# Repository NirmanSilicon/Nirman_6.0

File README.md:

# 🏥 Sanjeevani — Intelligent Healthcare & OPD Management Platform

<p align="center">
  <strong>Making Healthcare Smarter, Faster, and More Accessible.</strong>
</p>

<p align="center">
  An AI-powered healthcare navigation, OPD appointment, live queue management, and clinical assistance platform built for <strong>NIRMAN 6.0 — HACKNATION 2026</strong> by <strong>Team crozbit</strong>.
</p>

---

## 📑 Table of Contents

1. [Hackathon Information](#-hackathon-information)
2. [Problem Statement](#-problem-statement)
3. [Our Solution](#-our-solution)
4. [Key Features](#-key-features)
5. [How the System Works](#-how-the-system-works)
6. [System Architecture](#-system-architecture)
7. [Technology Stack](#-technology-stack)
8. [Project Folder Structure](#-project-folder-structure)
9. [Installation and Setup Instructions](#-installation-and-setup-instructions)
10. [Environment Variables](#-environment-variables)
11. [How to Run the Project](#-how-to-run-the-project)
12. [Demo Mode & Simulated Data](#-demo-mode--simulated-data)
13. [API Overview](#-api-overview)
14. [AI / ML Implementation](#-ai--ml-implementation)
15. [Database Design](#-database-design)
16. [Current Implementation Status](#-current-implementation-status)
17. [Limitations and Future Scope](#-limitations-and-future-scope)
18. [Troubleshooting](#-troubleshooting)
19. [Team Members and Contributions](#-team-members-and-contributions)
20. [Hackathon Submission Information](#-hackathon-submission-information)
21. [License](#-license)

---

## 🏆 Hackathon Information

| Field | Details |
| :--- | :--- |
| **Event** | NIRMAN 6.0 — HACKNATION 2026 |
| **Evaluation Stage** | First Progress Evaluation |
| **Team Name** | `crozbit` |
| **Project Name** | Sanjeevani (backend API internally initialized as HealX) |
| **Repository** | `https://github.com/ayusshs/Nirman_6.0` (branch: `crozbit`) |

---

## 🎯 Problem Statement

Patients and hospitals in traditional outpatient (OPD) ecosystems face persistent operational bottlenecks:

- **Long and unpredictable OPD waiting times** with no real-time visibility into queue progression.
- **Inefficient manual appointment and walk-in queue handling**, leading to overcrowding at hospital counters.
- **Difficulty identifying the right hospital or medical specialist** based on symptoms, distance, and current crowd levels.
- **Fragmented medical records and lab reports** that are hard for patients to interpret before consultations.
- **Limited real-time analytics** for hospital administrators to monitor department load and patient feedback.

---

## 💡 Our Solution

**Sanjeevani** unifies hospital discovery, OPD appointment booking, live Socket.IO queue tracking, AI-assisted symptom/report guidance, and hospital admin analytics into a single web platform:

- **Patients** can discover hospitals on an interactive map, get AI-ranked hospital recommendations, book OPD slots, track their live queue position and estimated wait time, upload lab reports/prescriptions for OCR + AI summarization, and chat with an AI healthcare assistant.
- **Hospital Admins & Superadmins** can manage appointments, advance live department queues, view AI-generated operational insights and patient clinical summaries, analyze patient feedback sentiment, and export appointment data as CSV.

> [!NOTE]
> AI-generated guidance and report summaries are informational only and do not replace professional medical diagnosis.

---

## ✨ Key Features

### Implemented in Repository
- **Hospital Discovery & Geospatial Routing**: Browse and search hospitals (`/hospitals`, `/hospitals/$id`), view specialties and doctor slots, and compute driving routes/ETAs using OSRM (`MapService`) and Leaflet maps.
- **Smart OPD Appointment Booking (`/book`)**: Multi-step booking flow with hospital, department/specialty, doctor, and slot selection, backed by `POST /api/patient/book` and walk-in support (`POST /api/walkin_book`).
- **Live OPD Queue Management**: Atomic queue numbering (`QueueService`), live wait-time calculation (`GET /api/patient/active-appointment`, `GET /api/hospital/<hospital_id>/queue`), and real-time `queue_update` broadcasts via Flask-SocketIO.
- **JWT Authentication & Role Separation (`/login`)**: Patient signup/login (`POST /api/auth/signup`, `POST /api/auth/login`) and Admin/Superadmin authentication using `flask-bcrypt` and `PyJWT`.
- **AI Multi-Agent Assistant (`MediBotChat`)**: Intent-routing AI assistant (`POST /api/chat`, `POST /api/ai/chat`) with specialized agents for appointments, queue status, hospital recommendations, report summaries, and medical Q&A, backed by local Ollama (`gemma3:4b`), RAG over `backend/knowledge/`, and rule-based offline fallbacks.
- **Medical Report Upload & AI Summary**: Upload PDFs or images (`POST /api/patient/upload_report`) parsed via `pdfplumber` / `easyocr` and summarized via Ollama.
- **Admin & Superadmin Operations**: Queue advancement (`POST /api/admin/queue/serve`), appointment status management, AI patient clinical briefs, feedback sentiment/topic analytics, CSV export, and platform-wide superadmin management.

### UI-Simulated / In-Progress Modules
- **Digital Pharmacy (`/pharmacy`)**: Interactive medicine catalog, cart drawer, and multi-step checkout UI using client-side data (`medicineData.ts`).
- **SOS Emergency Center (`/emergency`)**: First-aid guides and simulated ambulance dispatch telemetry using mock hospital coordinates.
- **Patient Portal Enhancements (`/dashboard`)**: Digital health card / ABHA-style ID display and vitals UI alongside live backend appointments and reports.

---

## 🔄 How the System Works

```mermaid
flowchart LR
    U[Patient] -->|1. Register / Login| Auth[JWT Auth API]
    U -->|2. Search Hospitals & Symptoms| Rec[Recommendation Engine + OSRM]
    U -->|3. Book OPD Slot| Book[POST /api/patient/book]
    Book --> Q[QueueService: Assign Token & Predict Wait]
    Q -->|Socket.IO queue_update| Dash[Patient Dashboard]
    Admin[Hospital Admin] -->|4. Serve Next Patient| Serve[POST /api/admin/queue/serve]
    Serve -->|Socket.IO queue_update| Dash
    U -->|5. Upload Lab Report / Chat| AI[AI Router + OCR + Ollama + RAG]
```

1. **Authentication**: A patient signs up or logs in at `/login`; the backend issues a 24-hour HS256 JWT stored in `localStorage`.
2. **Hospital Discovery**: The frontend calls `GET /api/hospital/` (auto-seeding sample Bhubaneswar hospitals via `POST /api/hospital/seed` if the database is empty) and `GET /api/hospital/search` for symptom-to-department + ML-ranked recommendations.
3. **Appointment & Queue Assignment**: Booking an appointment atomically increments `total_in_queue` in MongoDB, estimates wait time using `QueuePredictor` (XGBoost or rule-based fallback), and emits a Socket.IO `queue_update` event.
4. **Live Tracking & Admin Serving**: As admins advance the queue via `POST /api/admin/queue/serve` or update appointment statuses, the patient's `people_ahead` and `wait_time_predicted` recalculate live.
5. **AI & Report Assistance**: Patient chat messages pass through `AIRouter` (intent detection + conversation memory + RAG context + Ollama/fallback); uploaded reports pass through `ReportAnalyzer` (`pdfplumber` / `easyocr` + Ollama).

---

## 🏗️ System Architecture

```mermaid
flowchart TD
    subgraph Client ["Frontend (TanStack Start + React + Vite)"]
        UI[Pages: /, /hospitals, /book, /dashboard, /pharmacy, /emergency, /login]
        Map[Leaflet Interactive Map]
        Chat[MediBotChat Widget]
    end

    subgraph Server ["Backend (Flask + Flask-SocketIO)"]
        Routes[Blueprints: auth, patient, hospital, api, admin, superadmin, ai]
        Services[Services: QueueService, MapService, AIService]
        AIRouter[AI Router & Agents + RAG]
        ML[ML Predictors: Disease, Queue, Recommendation, Feedback]
    end

    subgraph Data ["Data & External Services"]
        Mongo[(MongoDB)]
        Redis[(Redis - Optional SocketIO Queue)]
        Ollama[Local Ollama LLM - gemma3:4b]
        OSRM[OSRM Routing API]
    end

    UI --> Routes
    Map --> Routes
    Chat --> Routes
    Routes --> Services
    Routes --> AIRouter
    Services --> ML
    Routes --> Mongo
    Services --> Mongo
    Services --> OSRM
    Server --> Redis
    AIRouter --> Ollama
```

- **Frontend (`frontend/`)**: Built with **TanStack Start**, **TanStack Router**, **TanStack Query**, **React 19**, **TypeScript**, and **Tailwind CSS v4**. Communicates with the Flask backend at `http://localhost:5000/api` (`frontend/src/lib/api.ts`).
- **Backend (`backend/`)**: Modular **Flask** application factory (`create_app()` in `backend/app/__init__.py`) registering 7 blueprints (`/api/auth`, `/api/patient`, `/api/hospital`, `/api`, `/api/admin`, `/api/superadmin`, `/api/ai`) with **Flask-SocketIO** for real-time queue events.
- **Database**: **MongoDB** via `pymongo` (`patients`, `hospitals`, `appointments`, `queue`, `queue_history`, `reports`, `admins`, `feedback` collections). **Redis** is optional for Socket.IO message queuing and falls back to an in-memory queue if unavailable.
- **AI/ML Layer**: Combines 4 `.joblib` scikit-learn/XGBoost/LightGBM models in `trained_models/`, a JSON-backed RAG store (`backend/trained_models/rag_index.json`), `pdfplumber`/`easyocr` document extraction, and local **Ollama** inference with deterministic fallbacks.

---

## 🛠️ Technology Stack

| Layer | Technologies Verified in Repository |
| :--- | :--- |
| **Frontend Framework** | React 19, TypeScript, TanStack Start, TanStack Router, TanStack Query, Vite 8 |
| **UI & Visualization** | Tailwind CSS v4, Radix UI, Lucide React, Recharts, Leaflet |
| **Forms & Validation** | React Hook Form, Zod |
| **Backend Framework** | Python, Flask, Flask-SocketIO, Flask-CORS, Flask-Bcrypt, PyJWT, Gunicorn |
| **Database & Messaging** | MongoDB (`pymongo`), Redis (optional Socket.IO message queue) |
| **AI / LLM & RAG** | Ollama (`gemma3:4b` default), `sentence-transformers`, `anthropic` (listed in `requirements.txt`), custom JSON RAG store |
| **ML & Data** | `scikit-learn`, `xgboost`, `lightgbm`, `pandas`, `numpy`, `joblib` |
| **OCR & PDF Parsing** | `easyocr`, `pdfplumber` |
| **Geospatial Routing** | OSRM (`router.project-osrm.org`), Leaflet |

---

## 📂 Project Folder Structure

```text
Nirman_6.0/
├── crozbit.txt                        # Hackathon & team identifier
├── trained_models/                    # Pre-trained ML model artifacts (.joblib)
│   ├── disease_risk_model.joblib
│   ├── feedback_sentiment_model.joblib
│   ├── queue_model.joblib
│   └── recommendation_model.joblib
│
├── backend/
│   ├── Procfile                       # Gunicorn process definition
│   ├── requirements.txt               # Python dependencies
│   ├── run.py                         # Flask-SocketIO entry point (port 5000)
│   ├── seed_superadmin.py             # Script to seed default superadmin
│   ├── test_*.py                      # Backend API, AI, routing, and signup test scripts
│   ├── knowledge/                     # RAG knowledge base (.txt files: faqs, hospitals, policies)
│   ├── ml/                            # Training scripts for the 4 ML models
│   ├── ml_models/train.py             # Additional ML training script
│   ├── trained_models/rag_index.json  # Pre-indexed RAG knowledge file
│   └── app/
│       ├── __init__.py                # Flask app factory, MongoDB, SocketIO, blueprints
│       ├── config.py                  # Environment configuration loader
│       ├── ai/                        # AI router, agents, Ollama client, RAG, ML predictors
│       ├── models/                    # MongoDB data access classes
│       ├── routes/                    # Flask blueprints (auth, patient, hospital, api, admin, superadmin, ai)
│       ├── services/                  # QueueService, MapService, AIService
│       └── utils/                     # Synthetic dataset generator
│
└── frontend/
    ├── package.json                   # Node dependencies & Vite scripts
    ├── vite.config.ts
    ├── tsconfig.json
    ├── public/                        # Static assets (logo.png, hero-video.mp4)
    └── src/
        ├── router.tsx                 # TanStack Router setup
        ├── routeTree.gen.ts           # Generated route tree
        ├── components/                # UI components (HospitalMap, MediBotChat, CameraCapture, etc.)
        ├── hooks/                     # Custom React hooks
        ├── lib/                       # API client (api.ts), mockData.ts, medicineData.ts, utils
        └── routes/                    # File-based routes (/, /login, /dashboard, /book, /hospitals, /pharmacy, /emergency, /about)
```

---

## ⚙️ Installation and Setup Instructions

### Prerequisites
- **Python 3.10+**
- **Node.js 18+** and **npm**
- **MongoDB** (local MongoDB Community Server or a MongoDB connection URI)
- **Ollama** (optional, for local LLM chat & report summarization; backend falls back to rule-based responses if Ollama is not running)
- **Redis** (optional; backend falls back to simple in-memory Socket.IO queue if unavailable)

### 1. Clone the Repository
```powershell
git clone https://github.com/ayusshs/Nirman_6.0.git
cd Nirman_6.0
```

### 2. Backend Setup (Windows PowerShell)
```powershell
cd backend
python -m venv .venv
.\.venv\Scripts\Activate.ps1
pip install -r requirements.txt
```

Create a `.env` file inside `backend/` (see [Environment Variables](#-environment-variables)).

*(Optional)* Seed the default superadmin account:
```powershell
python seed_superadmin.py
```

### 3. Frontend Setup (Windows PowerShell)
Open a new terminal in the repository root:
```powershell
cd frontend
npm install
```

---

## 🔐 Environment Variables

Create `backend/.env` using placeholders — **never commit `.env` or real credentials**:

```env
# Flask & JWT Security
SECRET_KEY=your_random_secret_key_here

# Database (Required for backend persistence)
MONGO_URI=mongodb://localhost:27017/sanjeevani

# Optional Redis for SocketIO message queue
REDIS_URL=redis://localhost:6379/0

# Optional Local LLM (Ollama)
LLM_PROVIDER=ollama
OLLAMA_BASE_URL=http://localhost:11434
OLLAMA_MODEL=gemma3:4b
DEFAULT_MODEL=gemma3:4b

# Optional External Keys (referenced in Config)
ANTHROPIC_API_KEY=your_anthropic_api_key_if_used
TWILIO_SID=your_twilio_sid_if_used
TWILIO_AUTH=your_twilio_auth_token_if_used
TWILIO_PHONE=your_twilio_phone_if_used
```

> [!IMPORTANT]
> `frontend/src/lib/api.ts` currently sets `API_BASE_URL = "http://localhost:5000/api"`. Ensure the backend runs on port `5000` during local development.

---

## ▶️ How to Run the Project

### Start the Backend Server
```powershell
cd backend
.\.venv\Scripts\Activate.ps1
python run.py
```
The Flask-SocketIO server starts on `http://localhost:5000`. Visiting `http://localhost:5000/` returns `{"message": "Welcome to HealX API"}`.

### Start the Frontend Development Server
```powershell
cd frontend
npm run dev
```
The Vite / TanStack Start dev server starts on `http://localhost:5173` (or the port printed in your terminal).

### Optional: Start Ollama for Local LLM Features
```powershell
ollama pull gemma3:4b
ollama serve
```

---

## 🧪 Demo Mode & Simulated Data

- **Auth-Gated Frontend Routes**: In `frontend/src/routes/__root.tsx`, navigating to `/dashboard` or `/book` checks `isLoggedIn()` (`localStorage.getItem("token")`) and redirects unauthenticated users to `/login`.
- **Automatic Hospital Seeding**: When `fetchHospitals()` receives an empty list from `GET /api/hospital/`, it automatically calls `POST /api/hospital/seed` to populate 3 sample Bhubaneswar hospitals (`SUM Hospital`, `AIIMS Bhubaneswar`, `Capital Hospital`).
- **Mock UI Enrichment (`frontend/src/lib/mockData.ts`)**: Backend hospital records are merged with mock bed counts, review counts, distances, and placeholder images for UI display.
- **Simulated Modules**:
  - `/pharmacy` uses static medicine catalog data (`medicineData.ts`) and a simulated checkout flow (e.g., coupon `SANJEEVANI30`, 3D card UI).
  - `/emergency` displays simulated ambulance tracking telemetry and static first-aid instructions.
  - `ReportAnalyzer` falls back to sample lab/MRI text if `EasyOCR` fails to initialize on an image upload.

---

## 📡 API Overview

All routes are mounted under `/api` (see `backend/app/__init__.py` and `backend/app/routes/`):

| Prefix | Method & Endpoint | Description |
| :--- | :--- | :--- |
| `/` | `GET /` | Health/welcome check |
| **Auth** (`/api/auth`) | `POST /api/auth/signup` | Register a new patient account |
| | `POST /api/auth/login` | Authenticate patient or admin/superadmin, returns JWT |
| **Patient** (`/api/patient`) | `GET /api/patient/profile` | Fetch patient profile, appointments, reports (JWT required) |
| | `PUT /api/patient/profile` | Update patient profile fields (JWT required) |
| | `GET /api/patient/active-appointment` | Fetch active appointment with live queue wait recalculation |
| | `GET /api/patient/appointments` | List all patient appointments |
| | `GET /api/patient/appointment/<booking_id>` | Get single appointment + embedded hospital info |
| | `POST /api/patient/book` | Book OPD appointment & assign queue token |
| | `POST /api/patient/upload_report` | Upload PDF/image report for OCR + AI summary |
| | `GET /api/patient/reports` | List uploaded patient reports |
| **Hospital** (`/api/hospital`) | `POST /api/hospital/seed` | Seed sample hospitals into MongoDB |
| | `GET /api/hospital/` | List all hospitals |
| | `GET /api/hospital/search` | Search & AI-rank hospitals by disease, state, query, `lat`/`lng` |
| | `GET /api/hospital/<hospital_id>` | Get hospital details and doctors |
| | `PUT /api/hospital/<hospital_id>` | Update hospital details |
| | `GET /api/hospital/<hospital_id>/route` | Get OSRM driving route from `start_lat`, `start_lng` |
| | `GET /api/hospital/<hospital_id>/queue` | Get live queue metrics per department |
| **Public / AI** (`/api`, `/api/ai`) | `POST /api/walkin_book` | Book a walk-in appointment without patient login |
| | `POST /api/chat` | Send message to `AIRouter` (with rule-based fallback) |
| | `POST /api/ai/chat` | Direct `AIRouter` chat endpoint |
| | `GET /api/reverse-geocode` | Reverse geocode `lat`, `lng` via `MapService` |
| **Admin** (`/api/admin`) | `GET /api/admin/appointments` | List appointments (filterable by `status`, `hospital_id`) |
| | `PUT /api/admin/appointments/<booking_id>/status` | Update appointment status & log queue history |
| | `POST /api/admin/queue/serve` | Increment `current_serving` & broadcast Socket.IO update |
| | `GET /api/admin/analytics` | Hospital appointment counts, queues, & AI insights |
| | `GET /api/admin/patient/<patient_id>/ai_summary` | Generate doctor brief via DiseasePredictor + Ollama |
| | `GET /api/admin/feedback_analytics` | Analyze review sentiment & common topics |
| | `GET /api/admin/export` | Export appointments as CSV |
| **Superadmin** (`/api/superadmin`) | `GET /api/superadmin/dashboard`, `/analytics` | Platform-wide counts (Superadmin JWT required) |
| | `GET / POST /api/superadmin/hospitals`, `PUT .../<id>` | Manage hospitals |
| | `GET / POST /api/superadmin/admins` | Manage hospital admins |

---

## 🤖 AI / ML Implementation

1. **Trained ML Models (`trained_models/*.joblib`, trained via `backend/ml/train_*.py` on synthetic/generated data)**:
   - **Disease Risk Predictor (`disease_risk_model.joblib`)**: `RandomForestClassifier` predicting `Low Risk`, `Medium Risk`, or `High Risk` from `age`, `bmi`, `sys_bp`, `sugar`, `smoking`, `exercise`, and `family_history` (falls back to a weighted rule score if the bundle is absent).
   - **Queue Wait-Time Predictor (`queue_model.joblib`)**: `XGBRegressor` predicting wait time in minutes using `people_ahead`, encoded `department`, `hour`, `weekday`, `holiday`, `emergency`, and `doctor_average_time` (falls back to `people_ahead * doctor_avg_time`).
   - **Hospital Recommendation Engine (`recommendation_model.joblib`)**: `LGBMRegressor` ranking hospitals using `distance`, `rating`, `queue_length`, `crowd_level`, `doctor_experience`, and `availability`.
   - **Feedback Sentiment Analyzer (`feedback_sentiment_model.joblib`)**: `TfidfVectorizer` + `MultinomialNB` pipeline classifying reviews as `positive`, `neutral`, or `negative`, paired with keyword-based topic extraction (`Waiting Time`, `Doctor Care`, `Billing`, `Cleanliness`, `General`).
2. **Multi-Agent AI Router & RAG (`backend/app/ai/`)**:
   - `AIRouter` classifies user messages into `appointment`, `queue_status`, `hospital_recommendation`, `report_summary`, `wallet_query`, or `medical_question` and dispatches to specialized agents.
   - `ContextBuilder` injects patient database context and RAG snippets from `backend/trained_models/rag_index.json` (built from `backend/knowledge/`).
   - `OllamaClient` queries `http://localhost:11434/api/chat` (`gemma3:4b` default) and gracefully degrades to keyword-based responses when Ollama is offline.
3. **Report Analyzer (`backend/app/ai/report_analyzer.py`)**:
   - Extracts text from PDFs (`pdfplumber`) and images (`easyocr`) and sends up to 1,200 characters to Ollama for a patient-friendly summary.

---

## 🗄️ Database Design

The backend uses **MongoDB** (`pymongo`) with the following collections:

| Collection | Key Fields & Purpose |
| :--- | :--- |
| `patients` | `patient_id` (`PAT-...`), `name`, `email`, `password_hash`, `gender`, `dob`, `bloodGroup`, `phone`, `emergency_contact`, `address`, `aadhar`, `insurance`, `tss_points`, `medicines`, `reports`, `bills` |
| `hospitals` | `hospital_id` (`HOSP-...`), `name`, `logo`, `address`, `location` (`city`, `state`, `lat`, `lng`), `workingHours`, `phone`, `email`, `specialties`, `departments`, `crowd_level`, `rating`, `doctors` |
| `appointments` | `booking_id` (`HLX-YYYYMMDD-DEPT-...`), `patient_id`, `hospital_id`, `doctor_id`, `department`, `slot_time`, `queue_number`, `status`, `wait_time_predicted`, `type`, `symptoms`, `paymentMode`, `paymentStatus`, `booked_at` |
| `queue` | `hospital_id`, `department`, `current_serving`, `total_in_queue`, `avg_time_per_patient`, `last_updated` (updated atomically via `find_one_and_update`) |
| `queue_history` | Event log of queue actions (`joined`, `served`, `completed`, `cancelled`, `no-show`) |
| `reports` | `patient_id`, `filename`, `extracted_text`, `ai_summary`, `uploaded_at` |
| `admins` | `admin_id` (`ADM-...`), `name`, `email`, `password_hash`, `role` (`admin` / `superadmin`), `hospitalId` |
| `feedback` | Patient review texts and departments used by `/api/admin/feedback_analytics` |

---

## 📊 Current Implementation Status

| Module | Status | Notes |
| :--- | :--- | :--- |
| Patient Auth (Signup / Login / JWT) | ✅ Implemented | `auth.py`, `login.tsx` |
| Hospital Listing, Seeding & Search | ✅ Implemented | `hospital.py`, `HospitalMap.tsx`, `mockData.ts` UI merge |
| OPD Booking & Live Queue Tracking | ✅ Implemented | `patient.py`, `QueueService`, Socket.IO |
| Admin Queue Serving, Analytics & CSV Export | ✅ Implemented | `admin.py`, `superadmin.py` |
| AI Router, ML Models & Report Analyzer | ✅ Implemented | Uses local Ollama + `.joblib` models trained on synthetic data; includes fallbacks |
| Digital Pharmacy (`/pharmacy`) | 🟡 Simulated UI | Static catalog (`medicineData.ts`) & simulated checkout |
| SOS Emergency & Ambulance Tracking (`/emergency`) | 🟡 Simulated UI | Static first-aid & mock ambulance telemetry |
| Android / Amazfit Bip 5 Wearable Integration | 🔵 Planned | Not yet present in repository |

---

## 🔭 Limitations and Future Scope

### Current Limitations
- ML models (`disease_risk_model`, `recommendation_model`, `feedback_sentiment_model`, `queue_model`) are trained on synthetic/generated datasets rather than live hospital clinical datasets.
- Frontend `API_BASE_URL` is hardcoded to `http://localhost:5000/api` in `frontend/src/lib/api.ts`.
- Admin and Superadmin routes have dedicated backend APIs, while the frontend primarily focuses on the patient portal.
- Pharmacy and Emergency modules currently operate on simulated frontend data.

### Future Scope
- Persist pharmacy orders and live ambulance dispatch telemetry in MongoDB.
- Build dedicated frontend portals for Hospital Admins and Superadmins.
- Add Android companion app integration for wearable queue/vibration alerts (e.g., Amazfit Bip 5).
- Retrain ML models on anonymized real-world OPD datasets and add automated CI tests.

---

## 🛠️ Troubleshooting

- **MongoDB Connection Error (`Error connecting to MongoDB`)**:
  - Verify MongoDB is running locally or your `MONGO_URI` in `backend/.env` is valid and reachable.
- **Redis Warning (`Could not connect to Redis, falling back to simple queue`)**:
  - Non-fatal. Flask-SocketIO automatically falls back to an in-memory queue for single-instance local development.
- **Ollama Offline Fallback**:
  - If Ollama is not running on `http://localhost:11434`, `OllamaClient` automatically returns rule-based fallback responses so `/api/chat` and `/api/patient/upload_report` do not crash.
- **Redirected to `/login` when opening `/dashboard` or `/book`**:
  - Expected behavior (`__root.tsx`). Sign up a new patient account at `/login` first to obtain a JWT token.
- **Empty Hospital List**:
  - Ensure the Flask backend is running on port `5000`; `fetchHospitals()` will automatically trigger `POST /api/hospital/seed` on first load.

---

## 👥 Team Members and Contributions

**Team:** `crozbit` (NIRMAN 6.0 — HACKNATION 2026)

| Member Name | Role / Focus Area | Contributions |
| :--- | :--- | :--- |
| `[Member 1 Name]` | Frontend & UI/UX | TanStack Start / React frontend, Leaflet maps, OPD booking & portal UI |
| `[Member 2 Name]` | Backend & Database | Flask APIs, MongoDB models, JWT auth, Socket.IO queue service |
| `[Member 3 Name]` | AI / ML & RAG | Multi-agent AI router, Ollama integration, `.joblib` ML models, OCR report analyzer |
| `[Member 4 Name]` | Testing & Integration | End-to-end testing, deployment config, documentation |

*(Replace placeholders above with actual team member names and verified role splits before final submission.)*

---

## 📝 Hackathon Submission Information

- **Hackathon**: NIRMAN 6.0 — HACKNATION 2026
- **Submission Milestone**: First Progress Evaluation
- **Team**: `crozbit`
- **Active Branch**: `crozbit`

---

## 📄 License

No `LICENSE` file is currently present in this repository. Add an appropriate open-source license (e.g., MIT) if required for final submission.

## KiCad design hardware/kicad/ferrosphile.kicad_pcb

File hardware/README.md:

# Ferrosphile hardware: carrier PCB

A 2-layer carrier board, 100 × 72 mm, all through-hole. The ESP32 DevKit, the tilt board and the compasses plug in, so nothing on the board is hard to solder.

- Schematic: [docs/ferrosphile-schematic.pdf](docs/ferrosphile-schematic.pdf)
- PCB layout (both copper layers): [docs/ferrosphile-pcb-layout.pdf](docs/ferrosphile-pcb-layout.pdf)
- Gerbers for ordering: [fabrication/ferrosphile-gerbers.zip](fabrication/ferrosphile-gerbers.zip)
- BOM: [fabrication/ferrosphile-bom.csv](fabrication/ferrosphile-bom.csv)

Checked in KiCad 8: **ERC 0 errors, DRC 0 violations, 0 unrouted pads, PCB matches schematic.**

## Folder layout

```
hardware/
  kicad/          KiCad 8 project (open ferrosphile.kicad_pro)
    ferrosphile.kicad_sym   custom symbols: ESP32 DevKit V1, GY-521
    ferrosphile.pretty/     custom footprint: ESP32 DevKit V1 (2 x 1x15 headers)
  fabrication/    Gerbers + drill files (zip), BOM
  docs/           schematic PDF/SVG/PNG, PCB previews
```

## What is on the board

| Block | Parts | What it does |
|---|---|---|
| LC oscillator | U1 74HC04, R1 1M, R2 1k, C1/C2 100n film, J1 coil | Pierce oscillator around the search coil, about 42 kHz. Metal near the coil shifts the frequency. |
| Buffer | U1B | Squares the signal for the ESP32 pulse counter |
| Brain | U2 ESP32 DevKit V1 (30-pin) | Reads all sensors, talks to a laptop over USB |
| Gradiometer | J2 tip compass, J3 top compass (GY-271) | Two QMC5883L boards. Bottom minus top cancels Earth's field. |
| Tilt | M1 GY-521 (MPU6050) | Corrects for how the probe is held |
| Display | J4 (optional) | 0.96" SSD1306 OLED |
| Controls | SW1 ZERO, SW2 RECORD | Zero (learn "nothing here") and record buttons |
| Power | J5, SW3, D1 1N5819 | Optional 5 V battery input. USB alone also works. |

## Pin map

| Net | ESP32 pin | Connects to |
|---|---|---|
| OSC_FREQ | GPIO34 | U1 pin 4 (buffered oscillator) |
| SDA0 / SCL0 | GPIO21 / GPIO22 | J2 tip compass (0x0D), M1 MPU6050 (0x68), J4 OLED (0x3C) |
| SDA1 / SCL1 | GPIO25 / GPIO26 | J3 top compass (0x0D) |
| BTN_ZERO | GPIO14 | SW1 to GND (internal pull-up) |
| BTN_REC | GPIO13 | SW2 to GND (internal pull-up) |
| VIN | VIN | J5 battery, through SW3 and D1 |
| +3V3 | 3V3 | U1 and all sensors |

Both compasses use address 0x0D, so each one gets its own I2C bus.

Connector pin order, printed on the board:
- J2 and J3: 3V3, GND, SCL, SDA
- J4: GND, VCC, SCL, SDA (the usual OLED order)
- J5: + then −

## Order the PCB

1. Upload `fabrication/ferrosphile-gerbers.zip` to JLCPCB, PCBWay or any PCB maker.
2. Settings: 2 layers, 1.6 mm, 100 × 72 mm, 1 oz copper, HASL. Any colour.
3. Smallest track is 0.3 mm and the smallest gap is 0.25 mm, so the cheapest standard option works.

**Before you order, measure your ESP32 board.** The footprint expects the two header rows 25.4 mm apart (DOIT DevKit V1, 30-pin). Some clones are 22.86 mm. If yours differs, edit `ferrosphile.pretty/ESP32_DevKit_V1_30pin.kicad_mod`.

## Extra parts to solder (not in the BOM)

- 2 × 1x15 female headers, 2.54 mm, for the ESP32
- 1 × 1x8 female header for the GY-521 (M1 is a socket)
- 1 × DIP-14 IC socket for the 74HC04
- 4-wire cables for the two compasses, twisted 2-wire cable for the coil

## Assembly order

1. Lowest parts first: R1, R2, D1 (stripe to the "K" side), C1, C2, C3.
2. DIP-14 socket, then buttons and the slide switch.
3. Screw terminals J1 and J5, pin headers J2, J3, J4.
4. Female headers for the ESP32 and the GY-521.
5. Before plugging anything in: check with a multimeter that 3V3 and GND are **not** shorted.
6. Plug in the 74HC04 (notch to the top), the ESP32 (USB end to the left) and the GY-521.

## Wiring the probe

- **Coil (J1):** 35–40 turns of 28 SWG enamelled wire on a 10 cm ring, about 250–300 µH. Scrape the enamel at the ends. Use twisted wire to the board.
- **Tip compass (J2):** in the probe tip, next to the coil.
- **Top compass (J3):** about 30 cm higher up the pole. The bigger the gap, the better the Earth's field cancels.
- Keep steel screws and magnets away from both compasses.

## Design notes

- C1 and C2 must be film capacitors. Ceramic ones drift with heat and cause fake readings.
- GPIO34 is input-only. That is fine here, because it only reads the oscillator.
- A ground pour covers both layers, except under the ESP32 antenna (keep-out zone).
- D1 stops USB power flowing back into the battery board when both are connected.
- Power nets use 0.5 mm tracks where there is room.

## Edit in KiCad

Install KiCad 8 or newer, then open `kicad/ferrosphile.kicad_pro`. The project carries its own symbol and footprint library, so it opens without extra setup.

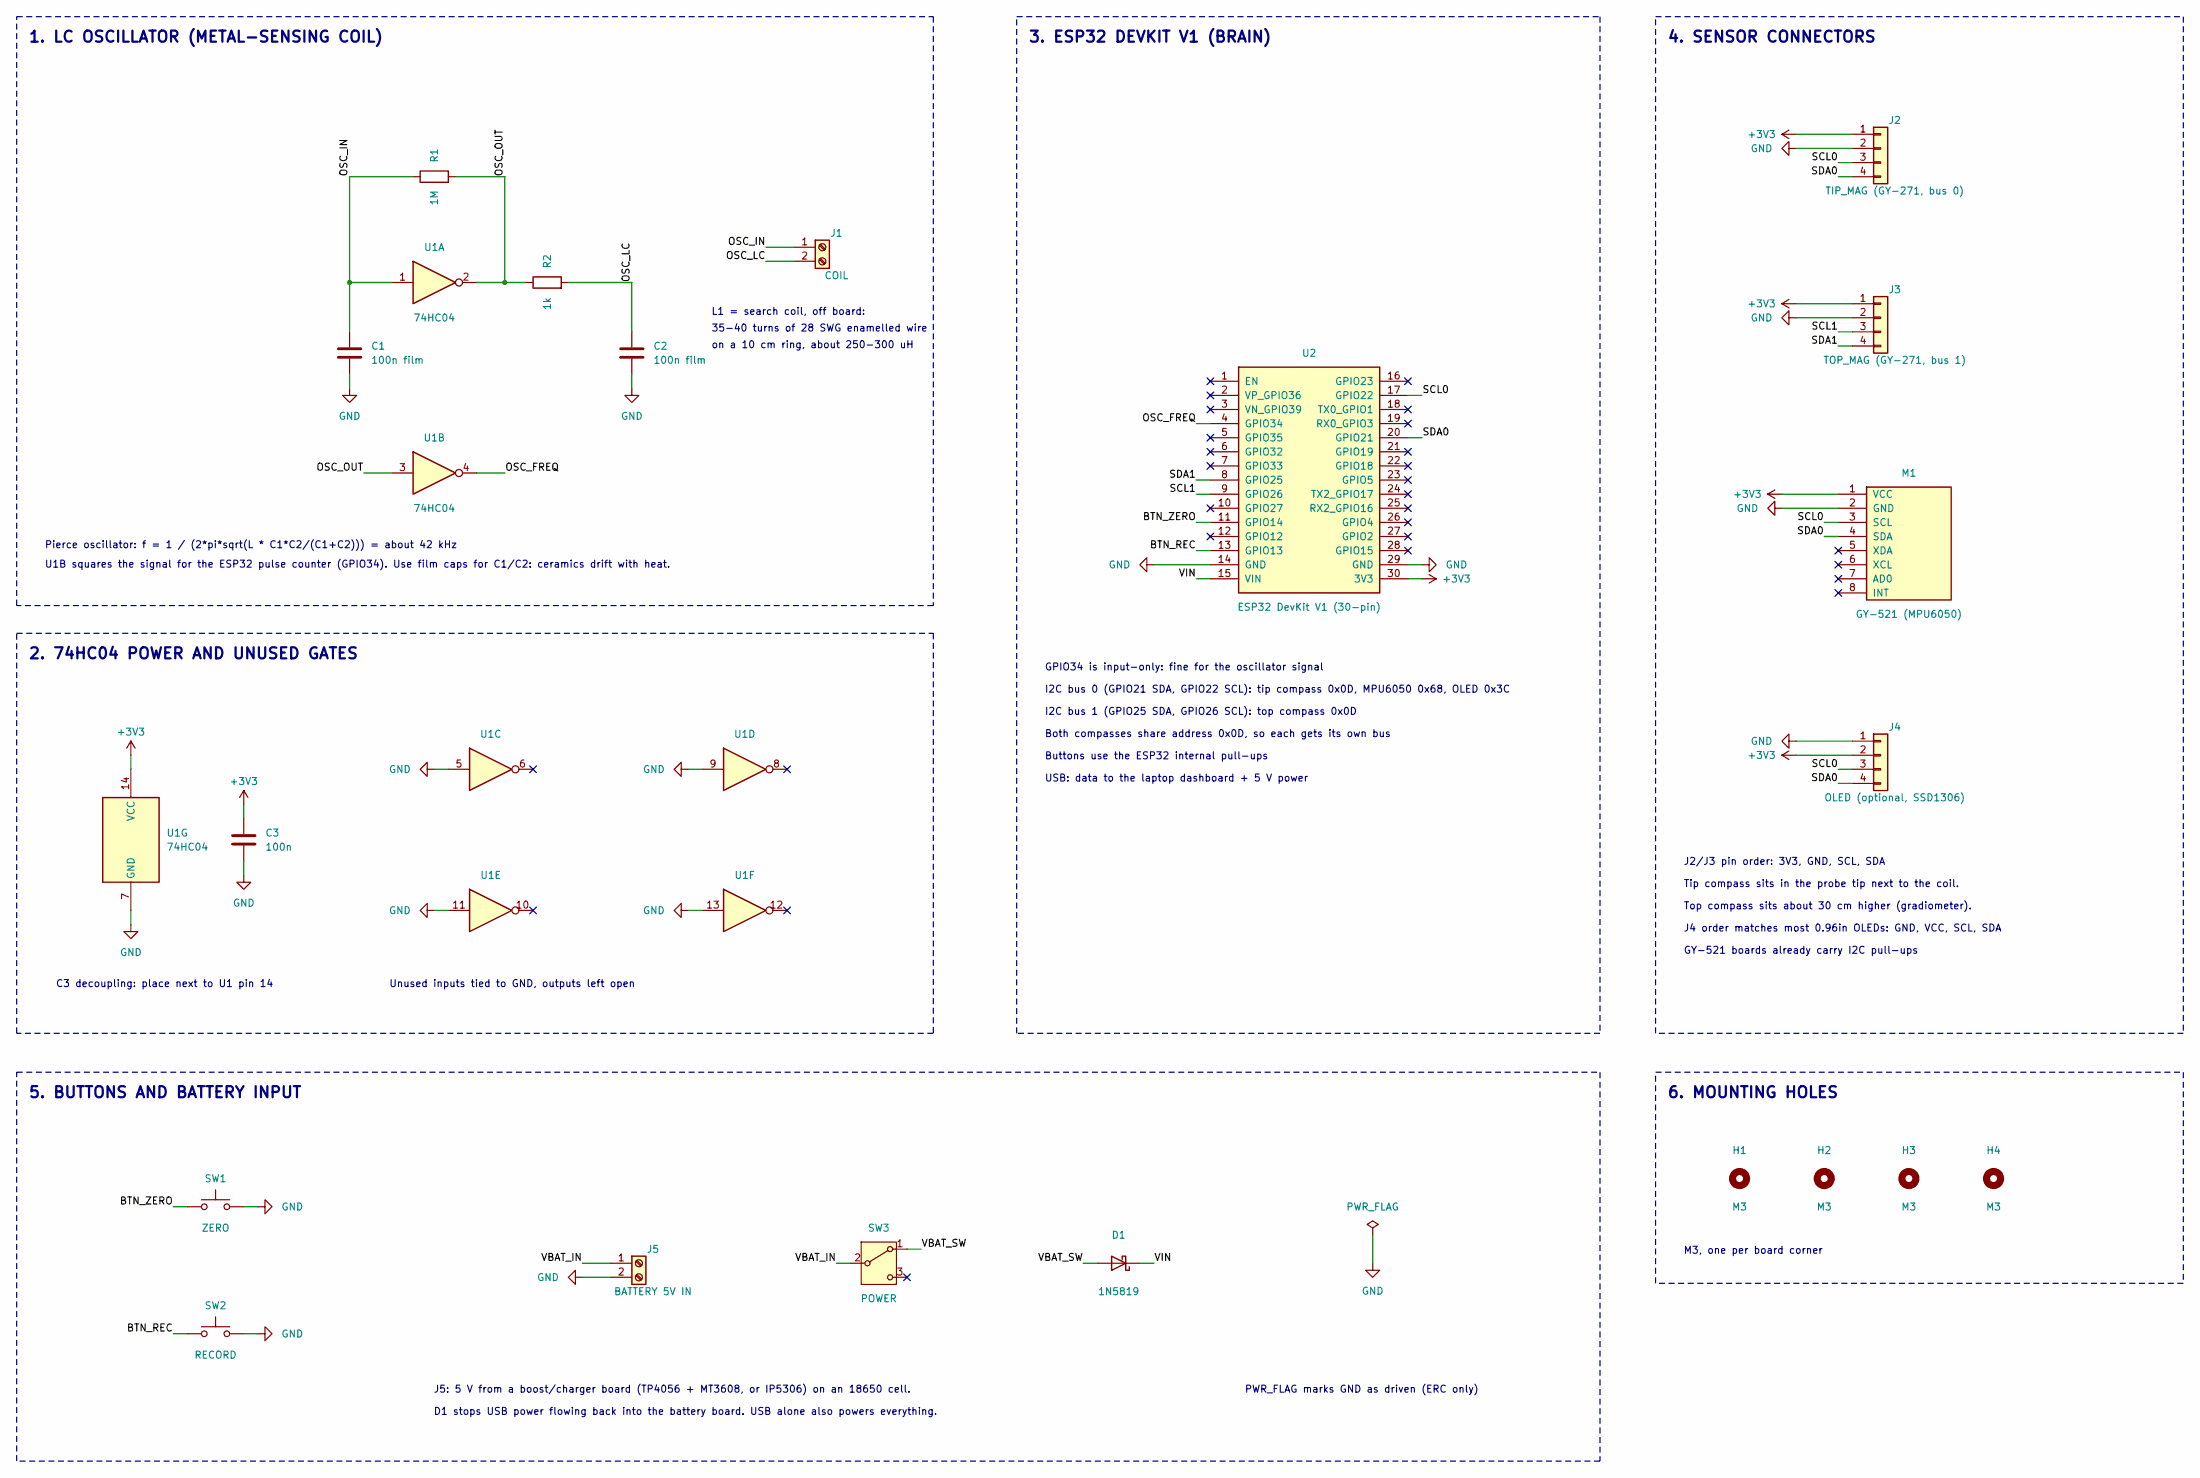
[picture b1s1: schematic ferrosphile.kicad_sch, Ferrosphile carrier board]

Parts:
C1, C2: 100n film; C_Rect_L7.2mm_W3.5mm_P5.00mm_FKS2_FKP2_MKS2_MKP2
C3: 100n; C_Disc_D5.0mm_W2.5mm_P5.00mm
D1: 1N5819; D_DO-41_SOD81_P10.16mm_Horizontal
H1, H2, H3, H4: M3; MountingHole_3.2mm_M3
J1: COIL; TerminalBlock_Phoenix_MKDS-1,5-2-5.08_1x02_P5.08mm_Horizont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
J2: TIP_MAG (GY-271, bus 0); PinHeader_1x04_P2.54mm_Vertical
J3: TOP_MAG (GY-271, bus 1); PinHeader_1x04_P2.54mm_Vertical
J4: OLED (optional, SSD1306); PinHeader_1x04_P2.54mm_Vertical
J5: BATTERY 5V IN; TerminalBlock_Phoenix_MKDS-1,5-2-5.08_1x02_P5.08mm_Horizont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
M1: GY-521 (MPU6050); PinSocket_1x08_P2.54mm_Vertical
R1: 1M; R_Axial_DIN0207_L6.3mm_D2.5mm_P10.16mm_Horizontal
R2: 1k; R_Axial_DIN0207_L6.3mm_D2.5mm_P10.16mm_Horizontal
SW1: ZERO; SW_PUSH_6mm
SW2: RECORD; SW_PUSH_6mm
SW3: POWER; SW_Slide_SPDT_Straight_CK_OS102011MS2Q
U1: 74HC04; DIP-14_W7.62mm_Socket
U2: ESP32 DevKit V1 (30-pin); ESP32_DevKit_V1_30pin

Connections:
+3V3: C3.1, J2.1, J3.1, J4.2, M1.1 (VCC), U1.14 (VCC), U2.30 (3V3)
/BTN_REC: SW2.1, U2.13 (GPIO13)
/BTN_ZERO: SW1.1, U2.11 (GPIO14)
/OSC_FREQ: U1.4, U2.4 (GPIO34)
/OSC_IN: C1.1, J1.1, R1.1, U1.1
/OSC_LC: C2.1, J1.2, R2.2
/OSC_OUT: R1.2, R2.1, U1.2, U1.3
/SCL0: J2.3, J4.3, M1.3 (SCL), U2.17 (GPIO22)
/SCL1: J3.3, U2.9 (GPIO26)
/SDA0: J2.4, J4.4, M1.4 (SDA), U2.20 (GPIO21)
/SDA1: J3.4, U2.8 (GPIO25)
/VBAT_IN: J5.1, SW3.2 (B)
/VBAT_SW: D1.2 (A), SW3.1 (A)
/VIN: D1.1 (K), U2.15 (VIN)
GND: C1.2, C2.2, C3.2, J2.2, J3.2, J4.1, J5.2, M1.2 (GND), SW1.2, SW2.2, U1.5, U1.7 (GND), U1.9, U1.11, U1.13, U2.14 (GND), U2.29 (GND)

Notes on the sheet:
1. LC OSCILLATOR (METAL-SENSING COIL)
L1 = search coil, off board:
35-40 turns of 28 SWG enamelled wire
on a 10 cm ring, about 250-300 uH
Pierce oscillator: f = 1 / (2*pi*sqrt(L * C1*C2/(C1+C2))) = about 42 kHz
U1B squares the signal for the ESP32 pulse counter (GPIO34). Use film caps for C1/C2: ceramics drift with heat.
2. 74HC04 POWER AND UNUSED GATES
C3 decoupling: place next to U1 pin 14
Unused inputs tied to GND, outputs left open
3. ESP32 DEVKIT V1 (BRAIN)
GPIO34 is input-only: fine for the oscillator signal
I2C bus 0 (GPIO21 SDA, GPIO22 SCL): tip compass 0x0D, MPU6050 0x68, OLED 0x3C
I2C bus 1 (GPIO25 SDA, GPIO26 SCL): top compass 0x0D
Both compasses share address 0x0D, so each gets its own bus
Buttons use the ESP32 internal pull-ups
USB: data to the laptop dashboard + 5 V power
4. SENSOR CONNECTORS
J2/J3 pin order: 3V3, GND, SCL, SDA
Tip compass sits in the probe tip next to the coil.
Top compass sits about 30 cm higher (gradiometer).
J4 order matches most 0.96in OLEDs: GND, VCC, SCL, SDA
GY-521 boards already carry I2C pull-ups
5. BUTTONS AND BATTERY INPUT
J5: 5 V from a boost/charger board (TP4056 + MT3608, or IP5306) on an 18650 cell.
D1 stops USB power flowing back into the battery board. USB alone also powers everything.
PWR_FLAG marks GND as driven (ERC only)
6. MOUNTING HOLES
M3, one per board corner

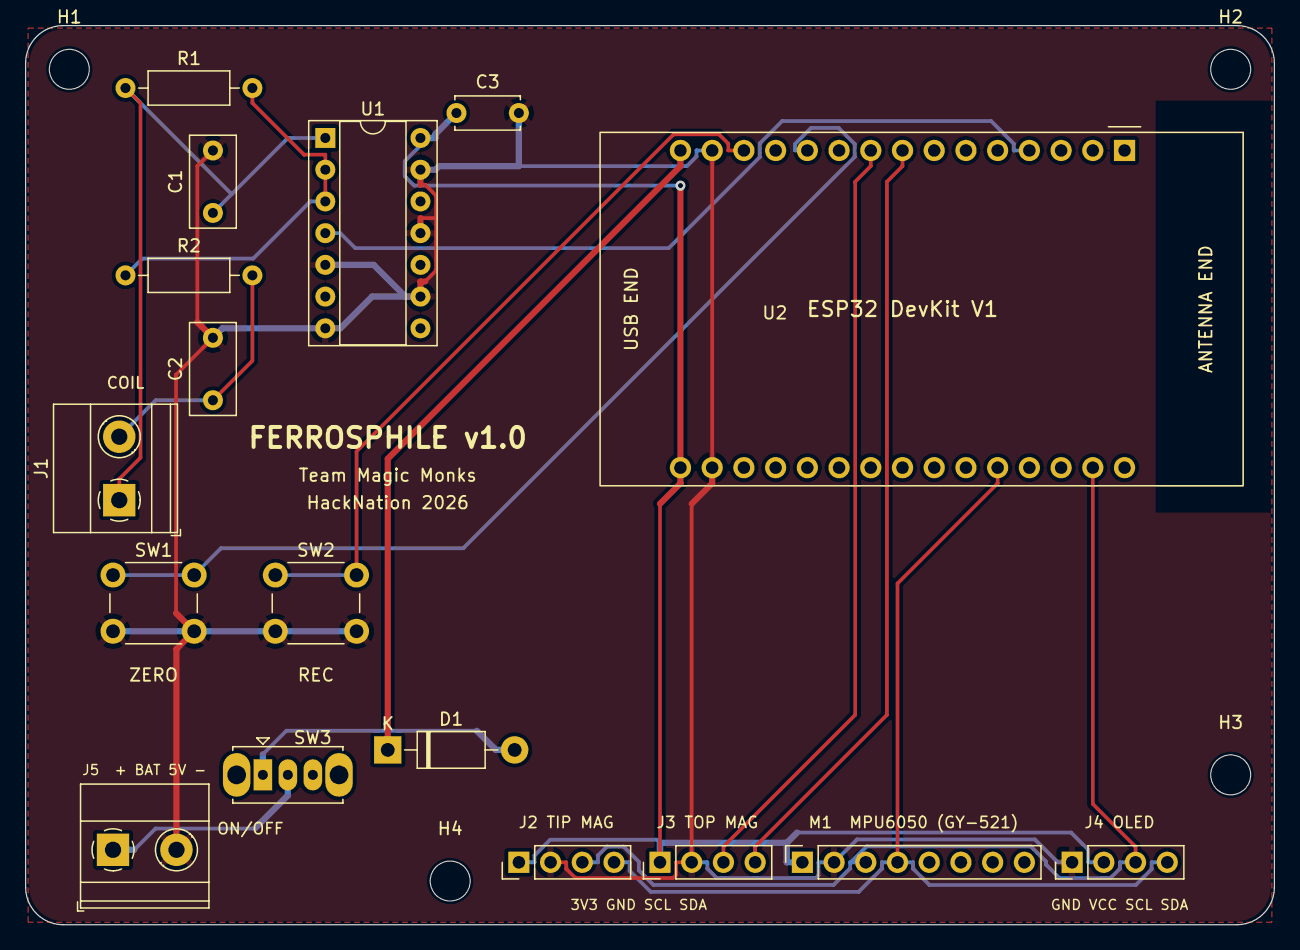
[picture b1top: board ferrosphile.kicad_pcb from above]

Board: 2 copper layers, 100.0 x 72.0 mm, 21 parts (0 on the bottom side), 15 nets.
